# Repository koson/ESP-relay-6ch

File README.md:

# ESP-relay-6ch

ESP8266/ESP32 based board with 6x 24 VDC inputs and 6x 10A relay outputs.

This board is designed to be driven by an Olimex ESP32-POE, ESP32-POE-ISO or Wemos D1 Mini modules running Tasmota. In case the Wemos D1 Mini is used, the number of inputs and outputs will be limited to 4 each.

The design considers that the board will be mounted on a PCB DIN rail holder. The dimensions consider the holders offered by the Brazilian manufacturer Metaltex, check [here](https://www.metaltex.com.br/produtos/componentes/suportes/sp7-suporte-para-montagem-de-placa-de-circuito-impresso-em-trilho-din) for details.

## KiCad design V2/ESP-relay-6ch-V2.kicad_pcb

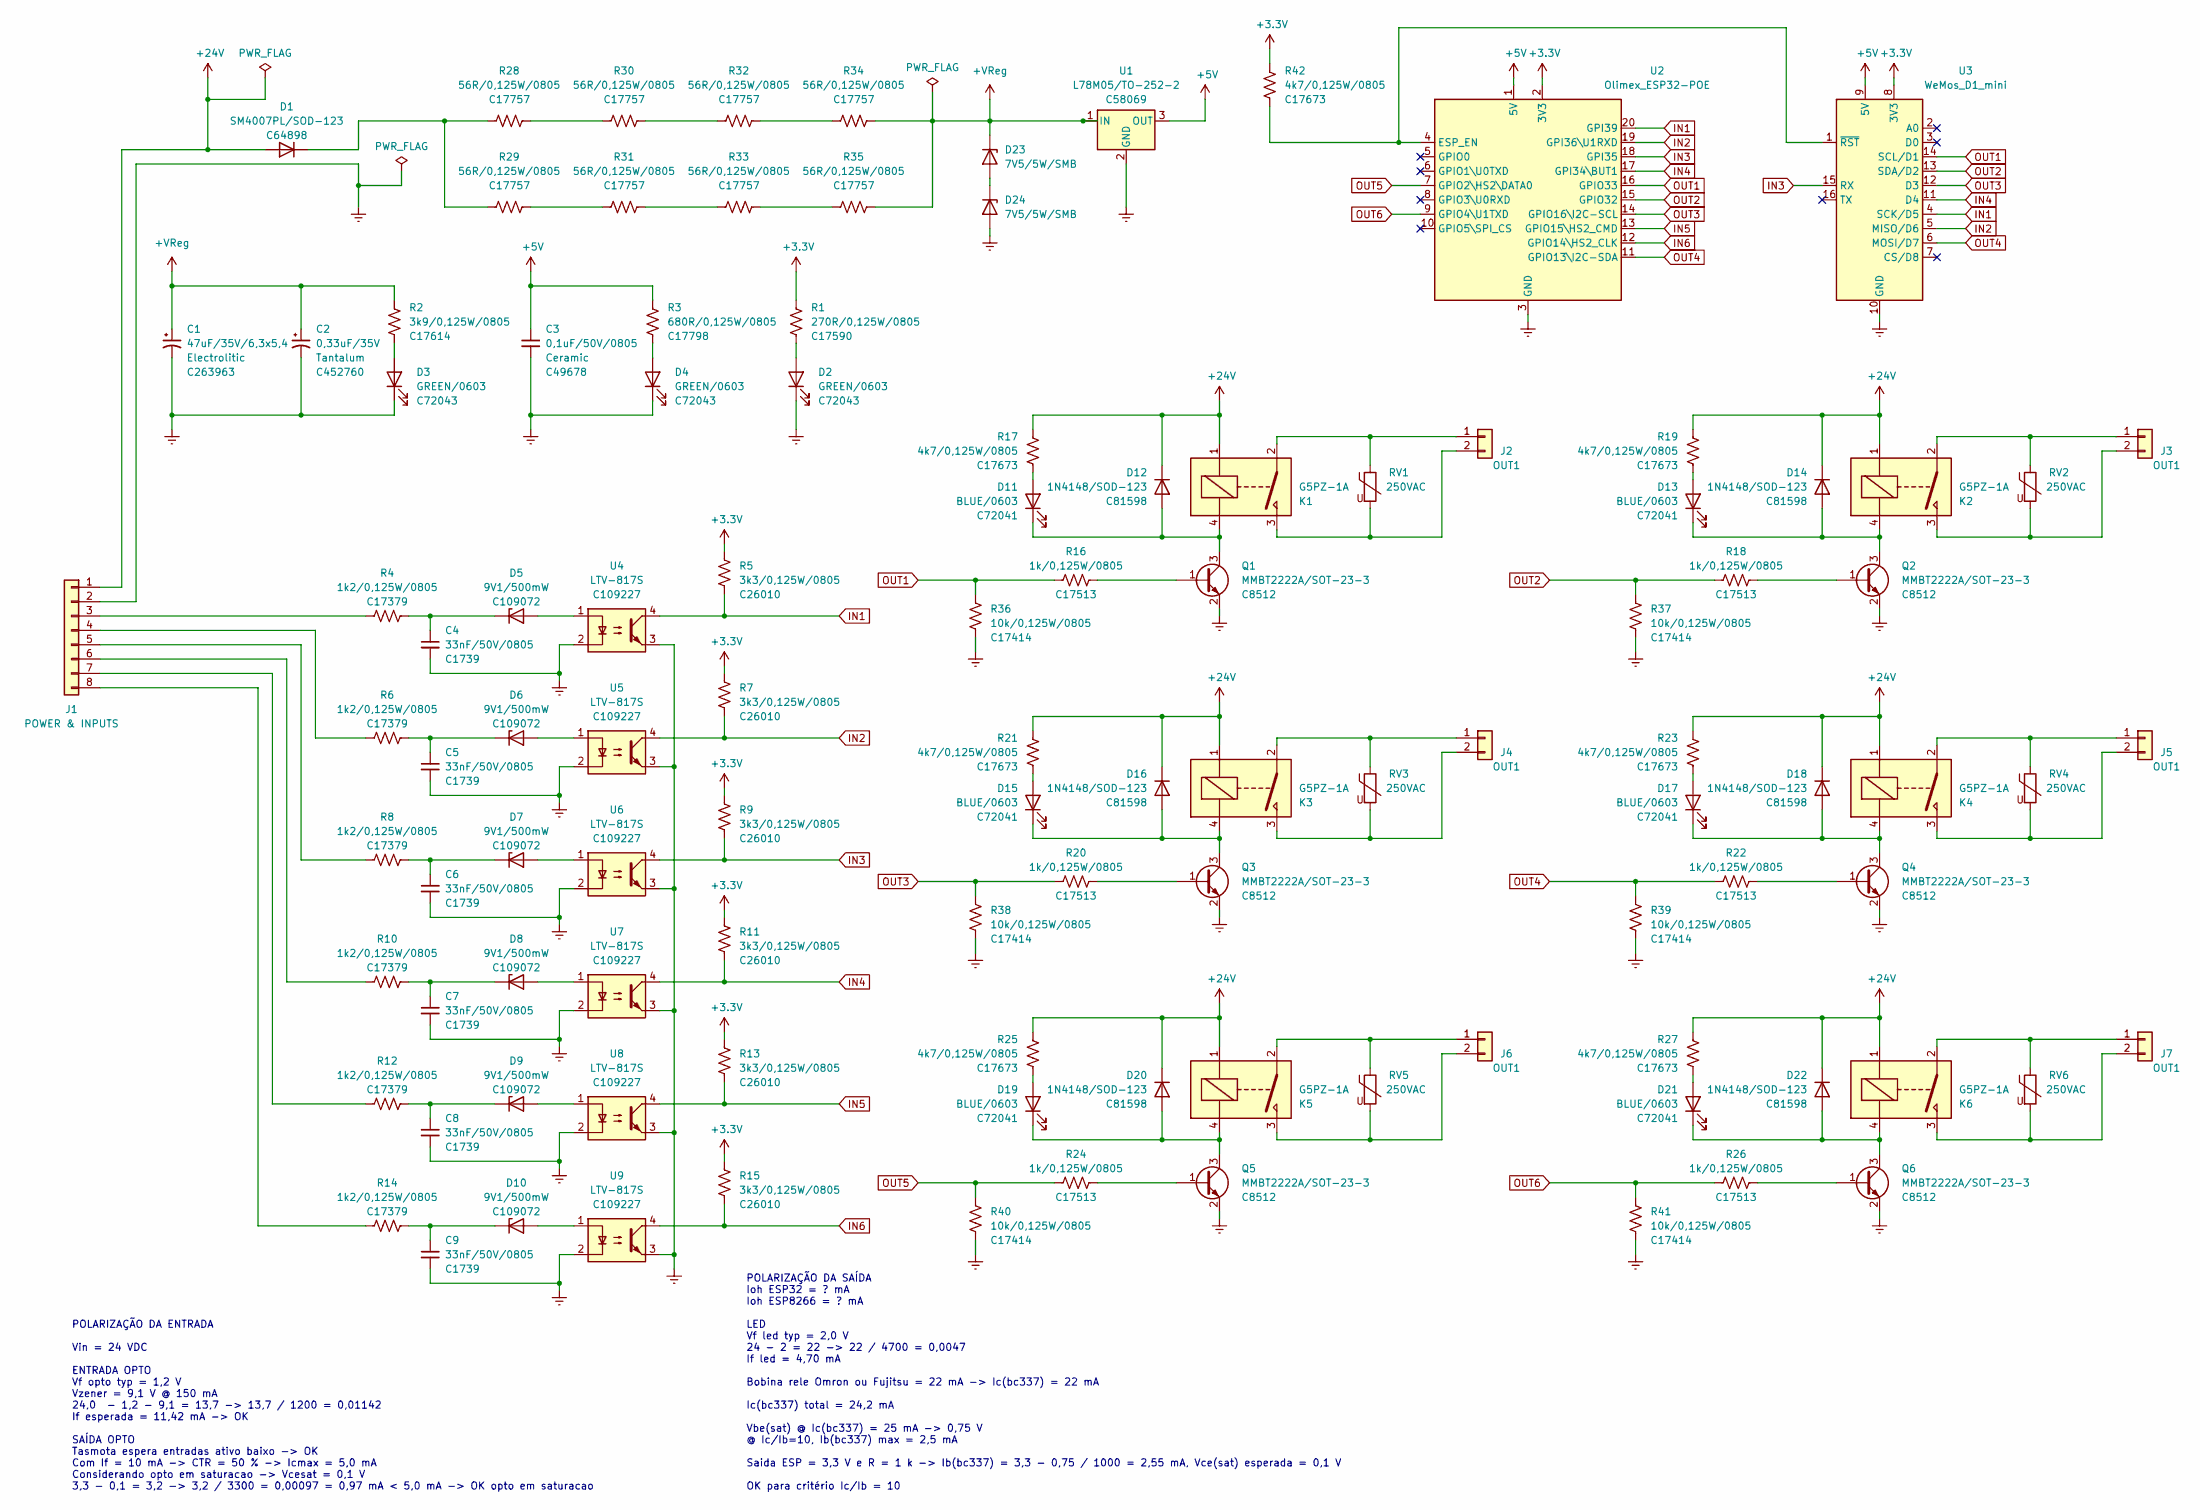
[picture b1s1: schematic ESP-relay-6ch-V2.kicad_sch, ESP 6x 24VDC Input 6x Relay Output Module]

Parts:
C1: 47uF/35V/6,3x5,4; CP_Elec_6.3x5.4; Mfr PN CK1V470MCRE54; JLCPCB BOM 1
C2: 0,33uF/35V; CP_EIA-3216-18_Kemet-A_Pad1.58x1.35mm_HandSolder; Mfr PN T491A334M035AT; JLCPCB BOM 1
C3: 0,1uF/50V/0805; C_0805_2012Metric; Mfr PN CC0805KRX7R9BB104; LCSC Part C49678
C4, C5, C6, C7, C8, C9: 33nF/50V/0805; C_0805_2012Metric; Mfr PN 0805B333K500NT; LCSC Part C1739
D1: SM4007PL/SOD-123; D_SOD-123; Mfr PN SM4007PL; LCSC Part C64898
D2, D3, D4: GREEN/0603; LED_0603_1608Metric; Mfr PN 19-217/GHC-YR1S2/3T; LCSC Part C72043
D5, D6, D7, D8, D9, D10: 9V1/500mW; D_MiniMELF; Mfr PN ZMM5239B; JLCPCB BOM 1
D11, D13, D15, D17, D19, D21: BLUE/0603; LED_0603_1608Metric; Mfr PN 19-217/BHC-ZL1M2RY/3T; LCSC Part C72041
D12, D14, D16, D18, D20, D22: 1N4148/SOD-123; D_SOD-123; Mfr PN 1N4148W; LCSC Part C81598
D23, D24: 7V5/5W/SMB; D_SMB; Mfr PN CZRB5343B-HF; JLCPCB BOM 0
J1: POWER & INPUTS; TerminalBlock_Phoenix_MKDS-3-8-5.08_1x08_P5.08mm_Horizontal; Mfr PN 3x BR902V; JLCPCB BOM 0
J2, J3, J4, J5, J6, J7: OUT1; TerminalBlock_Phoenix_MKDS-3-2-5.08_1x02_P5.08mm_Horizontal; Mfr PN BR902V; JLCPCB BOM 0
K1, K2, K3, K4, K5, K6: G5PZ-1A; Relay_SPST_Omron-G5PZ-1A; Mfr PN G5PZ-1A; JLCPCB BOM 0
Q1, Q2, Q3, Q4, Q5, Q6: MMBT2222A/SOT-23-3; SOT-23; Mfr PN MMBT2222A; JLCPCB BOM 1
R1: 270R/0,125W/0805; R_0805_2012Metric; Mfr PN 0805W8F2700T5E; LCSC Part C17590
R2: 3k9/0,125W/0805; R_0805_2012Metric; Mfr PN 0805W8F3901T5E; LCSC Part C17614
R3: 680R/0,125W/0805; R_0805_2012Metric; Mfr PN 0805W8F6800T5E; LCSC Part C17798
R4, R6, R8, R10, R12, R14: 1k2/0,125W/0805; R_0805_2012Metric; Mfr PN 0805W8F1201T5E; LCSC Part C17379
R5, R7, R9, R11, R13, R15: 3k3/0,125W/0805; R_0805_2012Metric; Mfr PN 0805W8F3301T5E; LCSC Part C26010
R16, R18, R20, R22, R24, R26: 1k/0,125W/0805; R_0805_2012Metric; Mfr PN 0805W8F1001T5E; LCSC Part C17513
R17, R19, R21, R23, R25, R27: 4k7/0,125W/0805; R_0805_2012Metric; Mfr PN 0805W8F4701T5E; LCSC Part C17673
R28, R29, R30, R31, R32, R33, R34, R35: 56R/0,125W/0805; R_0805_2012Metric; Mfr PN 0805W8F560JT5E; JLCPCB BOM 1
R36, R37, R38, R39, R40, R41: 10k/0,125W/0805; R_0805_2012Metric; Mfr PN 0805W8F3301T5E; LCSC Part C17414
R42: 4k7/0,125W/0805; R_0805_2012Metric; Mfr PN 0805W8F2700T5E; LCSC Part C17673
RV1, RV2, RV3, RV4, RV5, RV6: 250VAC; RV_Disc_D12mm_W3.9mm_P7.5mm; Mfr PN 391KD10; JLCPCB BOM 0
U1: L78M05/TO-252-2; TO-252-2; Mfr PN L78M05ABDT-TR; LCSC Part C58069
U2: Olimex_ESP32-POE; Olimex_ESP32-POE_Pads; Mfr PN ESP32-POE; JLCPCB BOM 0
U3: WeMos_D1_mini; WEMOS_D1_mini_light_pads; Mfr PN D1 Mini Node MCU; JLCPCB BOM 0
U4, U5, U6, U7, U8, U9: LTV-817S; SMDIP-4_W9.53mm; Mfr PN LTV-817S-TA1-C; JLCPCB BOM 1

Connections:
+3V3: R1.1, R5.1, R7.1, R9.1, R11.1, R13.1, R15.1, R42.1, U2.2 (3V3), U3.8 (3V3)
+5V: C3.1, R3.1, U1.3 (OUT), U2.1 (5V), U3.9 (5V)
+24V: D1.2 (A), D12.1 (K), D14.1 (K), D16.1 (K), D18.1 (K), D20.1 (K), D22.1 (K), J1.1, K1.1, K2.1, K3.1, K4.1, K5.1, K6.1, R17.1, R19.1, R21.1, R23.1, R25.1, R27.1
+VReg: C1.1, C2.1, D23.1 (K), R2.1, R34.2, R35.2, U1.1 (IN)
GNDREF: C1.2, C2.2, C3.2, C4.2, C5.2, C6.2, C7.2, C8.2, C9.2, D2.1 (K), D3.1 (K), D4.1 (K), D24.2 (A), J1.2, Q1.2 (E), Q2.2 (E), Q3.2 (E), Q4.2 (E), Q5.2 (E), Q6.2 (E), R36.2, R37.2, R38.2, R39.2, R40.2, R41.2, U1.2 (GND), U2.3 (GND), U3.10 (GND), U4.2, U4.3, U5.2, U5.3, U6.2, U6.3, U7.2, U7.3, U8.2, U8.3, U9.2, U9.3
IN1: R5.2, U2.20 (GPI39), U3.4 (SCK/D5), U4.4
IN2: R7.2, U2.19 (GPI36\U1RXD), U3.5 (MISO/D6), U5.4
IN3: R9.2, U2.18 (GPI35), U3.15 (RX), U6.4
IN4: R11.2, U2.17 (GPI34\BUT1), U3.11 (D4), U7.4
IN5: R13.2, U2.13 (GPIO15\HS2_CMD), U8.4
IN6: R15.2, U2.12 (GPIO14\HS2_CLK), U9.4
unnamed: C4.1, D5.1 (K), R4.1
unnamed: C5.1, D6.1 (K), R6.1
unnamed: C6.1, D7.1 (K), R8.1
unnamed: C7.1, D8.1 (K), R10.1
unnamed: C8.1, D9.1 (K), R12.1
unnamed: C9.1, D10.1 (K), R14.1
unnamed: D1.1 (K), R28.1, R29.1
unnamed: D2.2 (A), R1.2
unnamed: D3.2 (A), R2.2
unnamed: D4.2 (A), R3.2
unnamed: D5.2 (A), U4.1
unnamed: D6.2 (A), U5.1
unnamed: D7.2 (A), U6.1
unnamed: D8.2 (A), U7.1
unnamed: D9.2 (A), U8.1
unnamed: D10.2 (A), U9.1
unnamed: D11.1 (K), D12.2 (A), K1.4, Q1.3 (C)
unnamed: D11.2 (A), R17.2
unnamed: D13.1 (K), D14.2 (A), K2.4, Q2.3 (C)
unnamed: D13.2 (A), R19.2
unnamed: D15.1 (K), D16.2 (A), K3.4, Q3.3 (C)
unnamed: D15.2 (A), R21.2
unnamed: D17.1 (K), D18.2 (A), K4.4, Q4.3 (C)
unnamed: D17.2 (A), R23.2
unnamed: D19.1 (K), D20.2 (A), K5.4, Q5.3 (C)
unnamed: D19.2 (A), R25.2
unnamed: D21.1 (K), D22.2 (A), K6.4, Q6.3 (C)
unnamed: D21.2 (A), R27.2
unnamed: D23.2 (A), D24.1 (K)
unnamed: J1.3, R4.2
unnamed: J1.4, R6.2
unnamed: J1.5, R8.2
unnamed: J1.6, R10.2
unnamed: J1.7, R12.2
unnamed: J1.8, R14.2
unnamed: J2.1, K1.2, RV1.1
unnamed: J2.2, K1.3, RV1.2
unnamed: J3.1, K2.2, RV2.1
unnamed: J3.2, K2.3, RV2.2
unnamed: J4.1, K3.2, RV3.1
unnamed: J4.2, K3.3, RV3.2
unnamed: J5.1, K4.2, RV4.1
unnamed: J5.2, K4.3, RV4.2
unnamed: J6.1, K5.2, RV5.1
unnamed: J6.2, K5.3, RV5.2
unnamed: J7.1, K6.2, RV6.1
unnamed: J7.2, K6.3, RV6.2
unnamed: Q1.1 (B), R16.1
unnamed: Q2.1 (B), R18.1
unnamed: Q3.1 (B), R20.1
unnamed: Q4.1 (B), R22.1
unnamed: Q5.1 (B), R24.1
unnamed: Q6.1 (B), R26.1
unnamed: R28.2, R30.1
unnamed: R29.2, R31.1
unnamed: R30.2, R32.1
unnamed: R31.2, R33.1
unnamed: R32.2, R34.1
unnamed: R33.2, R35.1
unnamed: R42.2, U2.4 (ESP_EN), U3.1 (~RST)
OUT1: R16.2, R36.1, U2.16 (GPIO33), U3.14 (SCL/D1)
OUT2: R18.2, R37.1, U2.15 (GPIO32), U3.13 (SDA/D2)
OUT3: R20.2, R38.1, U2.14 (GPIO16\I2C-SCL), U3.12 (D3)
OUT4: R22.2, R39.1, U2.11 (GPIO13\I2C-SDA), U3.6 (MOSI/D7)
OUT5: R24.2, R40.1, U2.7 (GPIO2\HS2\DATA0)
OUT6: R26.2, R41.1, U2.9 (GPIO4\U1TXD)

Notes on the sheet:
POLARIZAÇÃO DA ENTRADA Vin = 24 VDC ENTRADA OPTO Vf opto typ = 1,2 V Vzener = 9,1 V @ 150 mA 24,0 - 1,2 - 9,1 = 13,7 -> 13,7 / 1200 = 0,01142 If esperada = 11,42 mA -> OK SAÍDA OPTO Tasmota espera entradas ativo baixo -> OK Com If = 10 mA -> CTR = 50 % -> Icmax = 5,0 mA Considerando opto em saturac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
POLARIZAÇÃO DA SAÍDA Ioh ESP32 = ? mA Ioh ESP8266 = ? mA LED Vf led typ = 2,0 V 24 - 2 = 22 -> 22 / 4700 = 0,0047 If led = 4,70 mA Bobina rele Omron ou Fujitsu = 22 mA -> Ic(bc337) = 22 mA Ic(bc337) total = 24,2 mA Vbe(sat) @ Ic(bc337) = 25 mA -> 0,75 V @ Ic/Ib=10, Ib(bc337) max = 2,5 mA Saida ESP 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

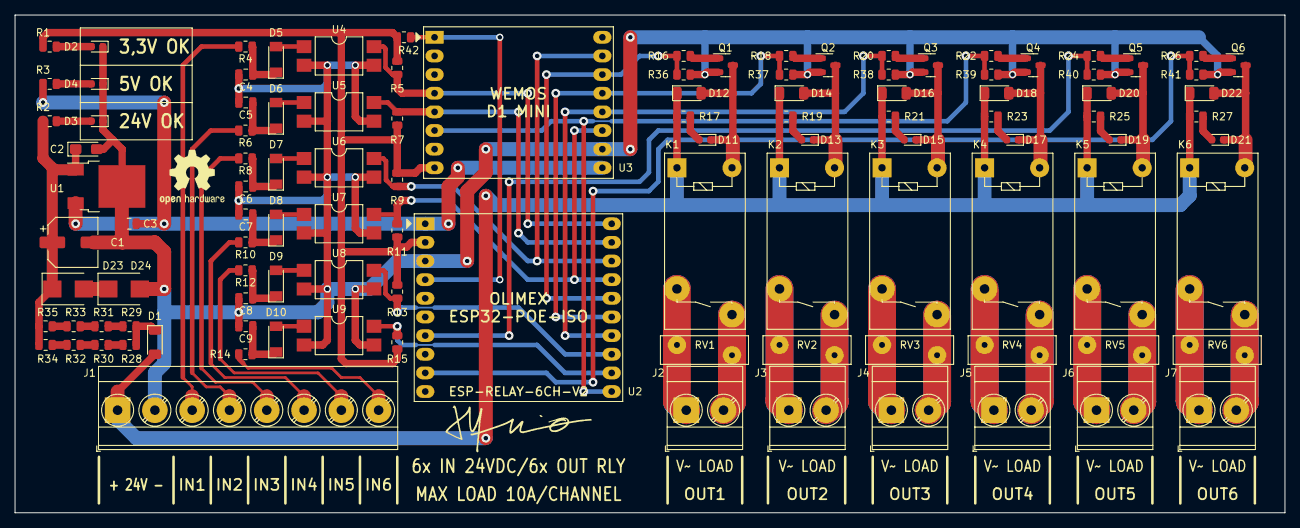
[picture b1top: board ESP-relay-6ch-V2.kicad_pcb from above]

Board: 2 copper layers, 173.0 x 67.8 mm, 109 parts (0 on the bottom side), 77 nets.

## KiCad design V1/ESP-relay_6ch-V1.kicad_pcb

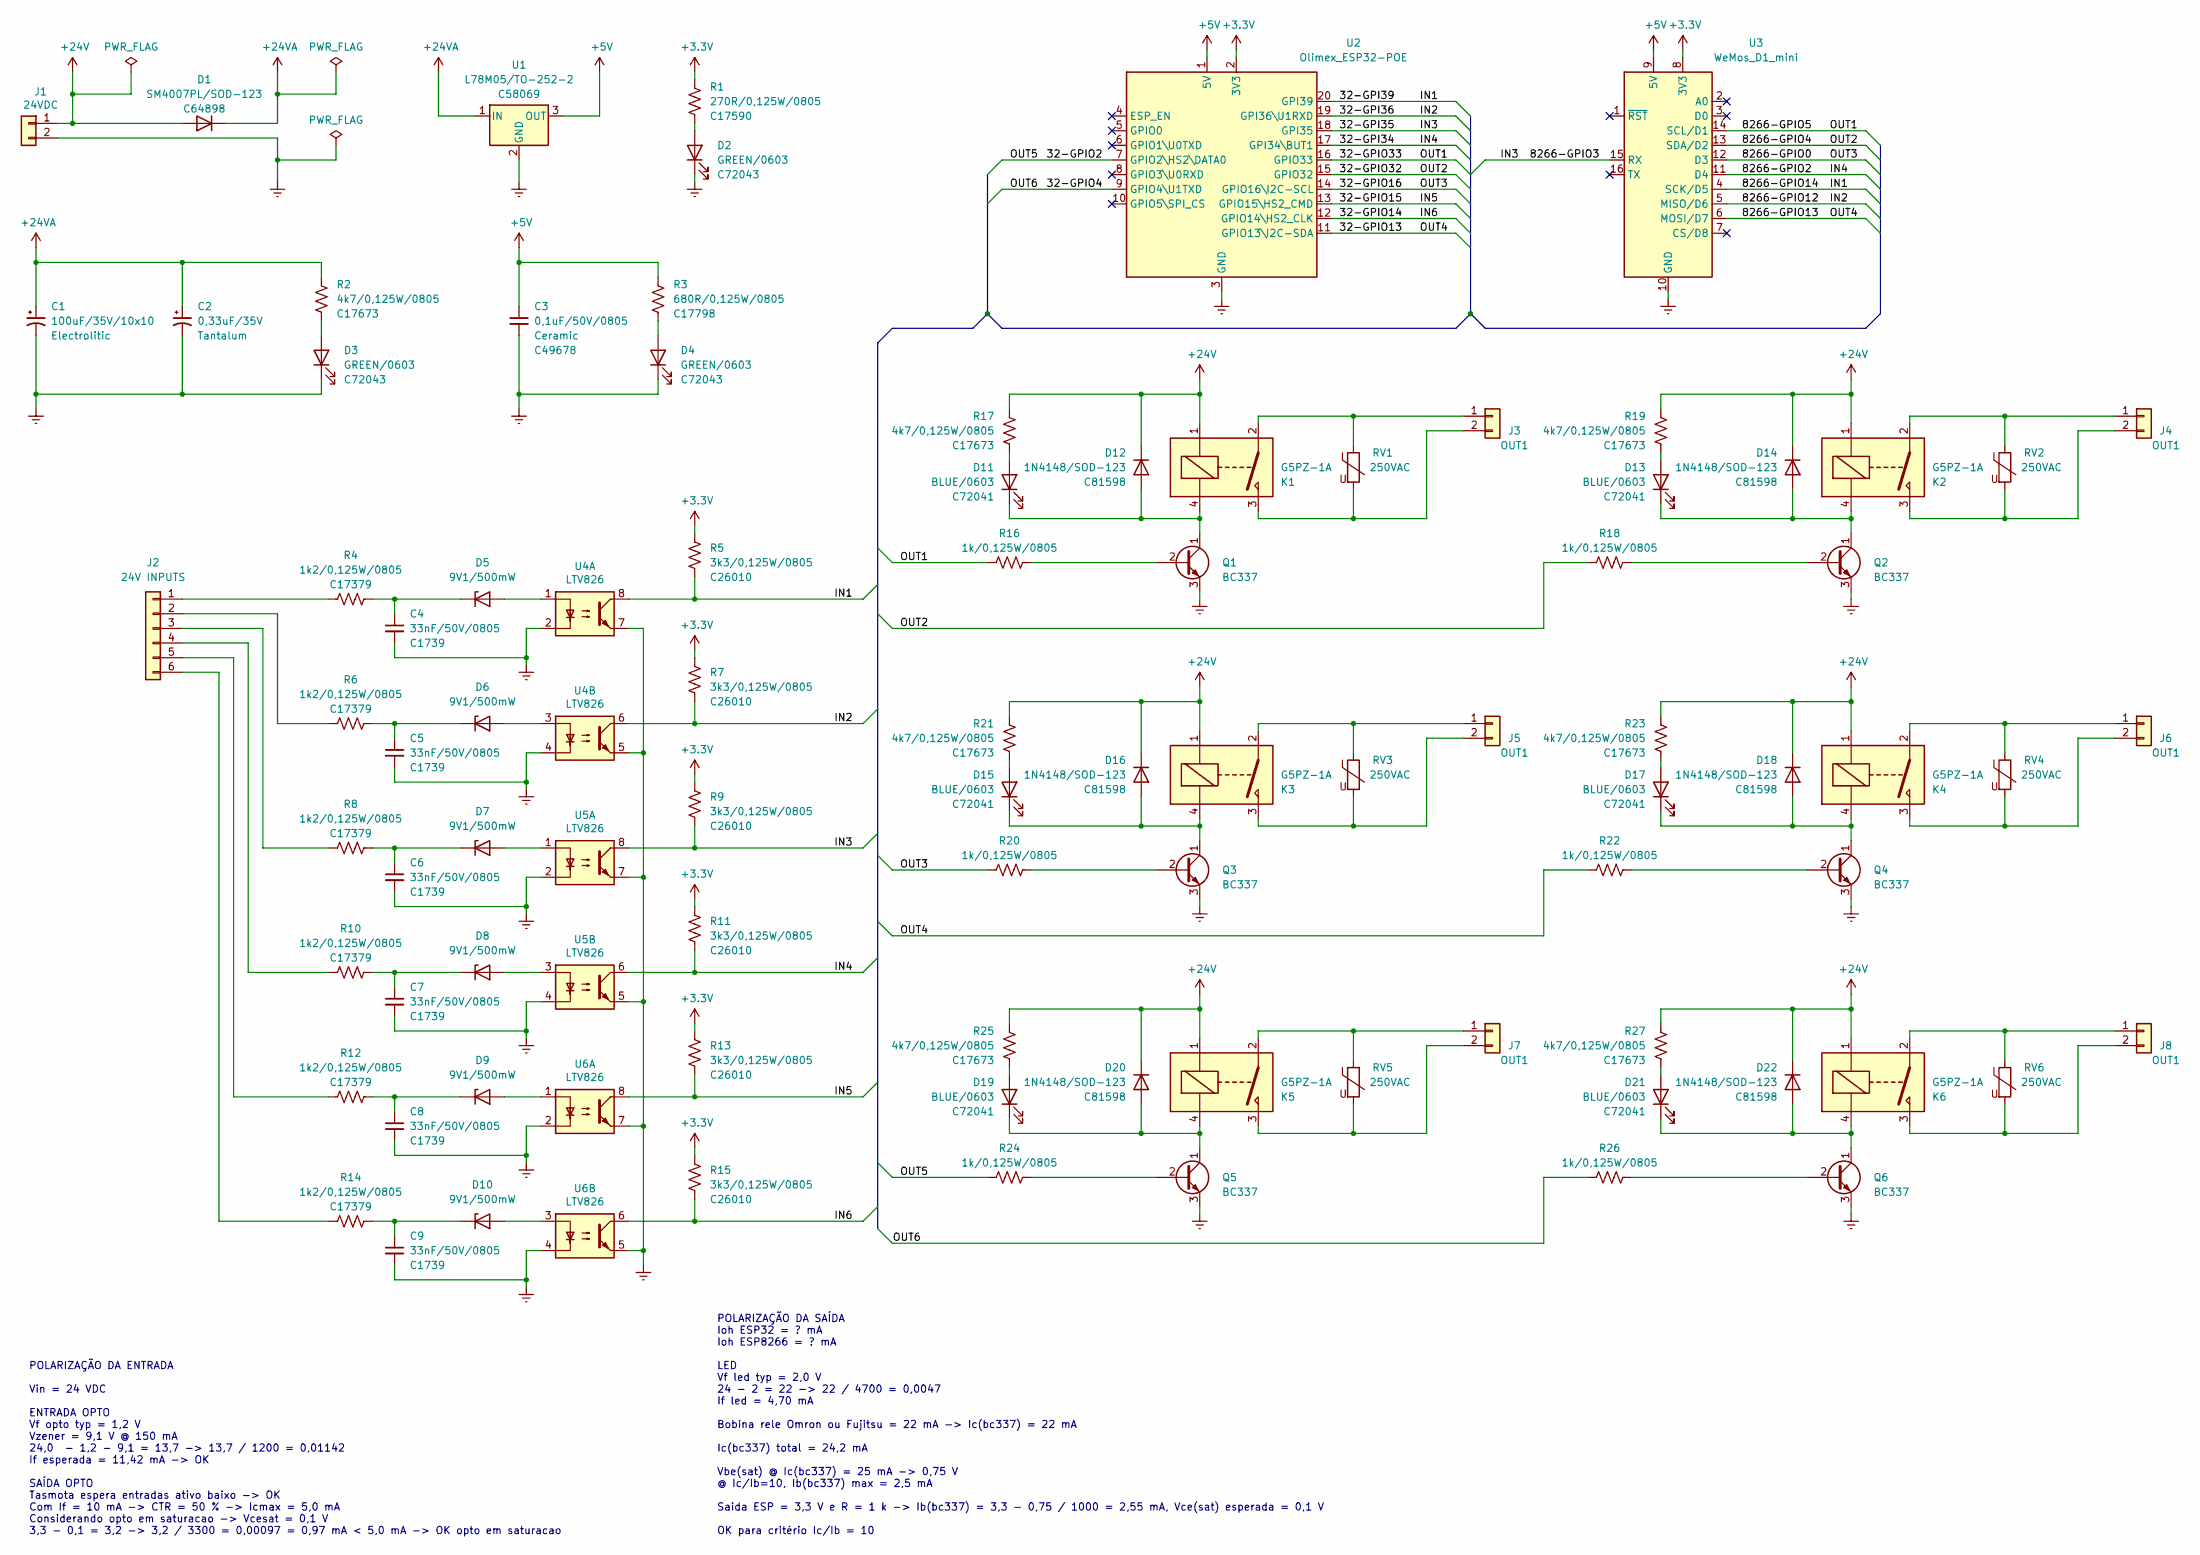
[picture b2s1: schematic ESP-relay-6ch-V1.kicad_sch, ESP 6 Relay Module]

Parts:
C1: 100uF/35V/10x10; CP_Elec_10x10; Mfr PN MAL214097001E3; JLCPCB BOM 0
C2: 0,33uF/35V; CP_EIA-3216-18_Kemet-A_Pad1.58x1.35mm_HandSolder; Mfr PN TAJA334K035RNJ; JLCPCB BOM 0
C3: 0,1uF/50V/0805; C_0805_2012Metric; Mfr PN CC0805KRX7R9BB104; LCSC Part C49678
C4, C5, C6, C7, C8, C9: 33nF/50V/0805; C_0805_2012Metric; Mfr PN 0805B333K500NT; LCSC Part C1739
D1: SM4007PL/SOD-123; D_SOD-123; Mfr PN SM4007PL; LCSC Part C64898
D2, D3, D4: GREEN/0603; LED_0603_1608Metric; Mfr PN 19-217/GHC-YR1S2/3T; LCSC Part C72043
D5, D6, D7, D8, D9, D10: 9V1/500mW; D_SOD-323; Mfr PN MM3Z9V1T1G; JLCPCB BOM 0
D11, D13, D15, D17, D19, D21: BLUE/0603; LED_0603_1608Metric; Mfr PN 19-217/BHC-ZL1M2RY/3T; LCSC Part C72041
D12, D14, D16, D18, D20, D22: 1N4148/SOD-123; D_SOD-123; Mfr PN 1N4148W; LCSC Part C81598
J1: 24VDC; TerminalBlock_Phoenix_MKDS-3-2-5.08_1x02_P5.08mm_Horizontal; Mfr PN BR902V; JLCPCB BOM 0
J2: 24V INPUTS; TerminalBlock_Phoenix_MKDS-3-6-5.08_1x06_P5.08mm_Horizontal; Mfr PN 3x BR902V; JLCPCB BOM 0
J3, J4, J5, J6, J7, J8: OUT1; TerminalBlock_Phoenix_MKDS-3-2-5.08_1x02_P5.08mm_Horizontal; Mfr PN BR902V; JLCPCB BOM 0
K1, K2, K3, K4, K5, K6: G5PZ-1A; Relay_SPST_Omron-G5PZ-1A; Mfr PN G5PZ-1A; JLCPCB BOM 0
Q1, Q2, Q3, Q4, Q5, Q6: BC337; TO-92_Inline_Wide; Mfr PN BC337-25; JLCPCB BOM 0
R1: 270R/0,125W/0805; R_0805_2012Metric; Mfr PN 0805W8F2700T5E; LCSC Part C17590
R2, R17, R19, R21, R23, R25, R27: 4k7/0,125W/0805; R_0805_2012Metric; Mfr PN 0805W8F4701T5E; LCSC Part C17673
R3: 680R/0,125W/0805; R_0805_2012Metric; Mfr PN 0805W8F6800T5E; LCSC Part C17798
R4, R6, R8, R10, R12, R14: 1k2/0,125W/0805; R_0805_2012Metric; Mfr PN 0805W8F1201T5E; LCSC Part C17379
R5, R7, R9, R11, R13, R15: 3k3/0,125W/0805; R_0805_2012Metric; Mfr PN 0805W8F3301T5E; LCSC Part C26010
R16, R18, R20, R22, R24, R26: 1k/0,125W/0805; R_0805_2012Metric; Mfr PN 0805W8F1001T5E; LCSC Part C17513
RV1, RV2, RV3, RV4, RV5, RV6: 250VAC; RV_Disc_D12mm_W3.9mm_P7.5mm; Mfr PN 391KD10; JLCPCB BOM 0
U1: L78M05/TO-252-2; TO-252-2; Mfr PN L78M05ABDT-TR; LCSC Part C58069
U2: Olimex_ESP32-POE; Olimex_ESP32-POE_Pads; Mfr PN ESP32-POE; JLCPCB BOM 0
U3: WeMos_D1_mini; WEMOS_D1_mini_light_pads; Mfr PN D1 Mini Node MCU; JLCPCB BOM 0
U4, U5, U6: LTV826; DIP-8_W7.62mm; Mfr PN LTV-826; JLCPCB BOM 0

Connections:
+3V3: R1.1, R5.1, R7.1, R9.1, R11.1, R13.1, R15.1, U2.2 (3V3), U3.8 (3V3)
+5V: C3.1, R3.1, U1.3 (OUT), U2.1 (5V), U3.9 (5V)
+24V: D1.2 (A), D12.1 (K), D14.1 (K), D16.1 (K), D18.1 (K), D20.1 (K), D22.1 (K), J1.1, K1.1, K2.1, K3.1, K4.1, K5.1, K6.1, R17.1, R19.1, R21.1, R23.1, R25.1, R27.1
+24VA: C1.1, C2.1, D1.1 (K), R2.1, U1.1 (IN)
/32-GPI34: R11.2, U2.17 (GPI34\BUT1), U3.11 (D4), U5.6
/32-GPI35: R9.2, U2.18 (GPI35), U3.15 (RX), U5.8
/32-GPI36: R7.2, U2.19 (GPI36\U1RXD), U3.5 (MISO/D6), U4.6
/32-GPI39: R5.2, U2.20 (GPI39), U3.4 (SCK/D5), U4.8
/32-GPIO2: R24.2, U2.7 (GPIO2\HS2\DATA0)
/32-GPIO4: R26.2, U2.9 (GPIO4\U1TXD)
/32-GPIO13: R22.2, U2.11 (GPIO13\I2C-SDA), U3.6 (MOSI/D7)
/32-GPIO14: R15.2, U2.12 (GPIO14\HS2_CLK), U6.6
/32-GPIO15: R13.2, U2.13 (GPIO15\HS2_CMD), U6.8
/32-GPIO16: R20.2, U2.14 (GPIO16\I2C-SCL), U3.12 (D3)
/32-GPIO32: R18.2, U2.15 (GPIO32), U3.13 (SDA/D2)
/32-GPIO33: R16.2, U2.16 (GPIO33), U3.14 (SCL/D1)
GNDREF: C1.2, C2.2, C3.2, C4.2, C5.2, C6.2, C7.2, C8.2, C9.2, D2.1 (K), D3.1 (K), D4.1 (K), J1.2, Q1.3 (E), Q2.3 (E), Q3.3 (E), Q4.3 (E), Q5.3 (E), Q6.3 (E), U1.2 (GND), U2.3 (GND), U3.10 (GND), U4.2, U4.4, U4.5, U4.7, U5.2, U5.4, U5.5, U5.7, U6.2, U6.4, U6.5, U6.7
unnamed: C4.1, D5.1 (K), R4.1
unnamed: C5.1, D6.1 (K), R6.1
unnamed: C6.1, D7.1 (K), R8.1
unnamed: C7.1, D8.1 (K), R10.1
unnamed: C8.1, D9.1 (K), R12.1
unnamed: C9.1, D10.1 (K), R14.1
unnamed: D2.2 (A), R1.2
unnamed: D3.2 (A), R2.2
unnamed: D4.2 (A), R3.2
unnamed: D5.2 (A), U4.1
unnamed: D6.2 (A), U4.3
unnamed: D7.2 (A), U5.1
unnamed: D8.2 (A), U5.3
unnamed: D9.2 (A), U6.1
unnamed: D10.2 (A), U6.3
unnamed: D11.1 (K), D12.2 (A), K1.4, Q1.1 (C)
unnamed: D11.2 (A), R17.2
unnamed: D13.1 (K), D14.2 (A), K2.4, Q2.1 (C)
unnamed: D13.2 (A), R19.2
unnamed: D15.1 (K), D16.2 (A), K3.4, Q3.1 (C)
unnamed: D15.2 (A), R21.2
unnamed: D17.1 (K), D18.2 (A), K4.4, Q4.1 (C)
unnamed: D17.2 (A), R23.2
unnamed: D19.1 (K), D20.2 (A), K5.4, Q5.1 (C)
unnamed: D19.2 (A), R25.2
unnamed: D21.1 (K), D22.2 (A), K6.4, Q6.1 (C)
unnamed: D21.2 (A), R27.2
unnamed: J2.1, R4.2
unnamed: J2.2, R6.2
unnamed: J2.3, R8.2
unnamed: J2.4, R10.2
unnamed: J2.5, R12.2
unnamed: J2.6, R14.2
unnamed: J3.1, K1.2, RV1.1
unnamed: J3.2, K1.3, RV1.2
unnamed: J4.1, K2.2, RV2.1
unnamed: J4.2, K2.3, RV2.2
unnamed: J5.1, K3.2, RV3.1
unnamed: J5.2, K3.3, RV3.2
unnamed: J6.1, K4.2, RV4.1
unnamed: J6.2, K4.3, RV4.2
unnamed: J7.1, K5.2, RV5.1
unnamed: J7.2, K5.3, RV5.2
unnamed: J8.1, K6.2, RV6.1
unnamed: J8.2, K6.3, RV6.2
unnamed: Q1.2 (B), R16.1
unnamed: Q2.2 (B), R18.1
unnamed: Q3.2 (B), R20.1
unnamed: Q4.2 (B), R22.1
unnamed: Q5.2 (B), R24.1
unnamed: Q6.2 (B), R26.1

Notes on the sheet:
POLARIZAÇÃO DA ENTRADA Vin = 24 VDC ENTRADA OPTO Vf opto typ = 1,2 V Vzener = 9,1 V @ 150 mA 24,0 - 1,2 - 9,1 = 13,7 -> 13,7 / 1200 = 0,01142 If esperada = 11,42 mA -> OK SAÍDA OPTO Tasmota espera entradas ativo baixo -> OK Com If = 10 mA -> CTR = 50 % -> Icmax = 5,0 mA Considerando opto em saturac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
POLARIZAÇÃO DA SAÍDA Ioh ESP32 = ? mA Ioh ESP8266 = ? mA LED Vf led typ = 2,0 V 24 - 2 = 22 -> 22 / 4700 = 0,0047 If led = 4,70 mA Bobina rele Omron ou Fujitsu = 22 mA -> Ic(bc337) = 22 mA Ic(bc337) total = 24,2 mA Vbe(sat) @ Ic(bc337) = 25 mA -> 0,75 V @ Ic/Ib=10, Ib(bc337) max = 2,5 mA Saida ESP 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

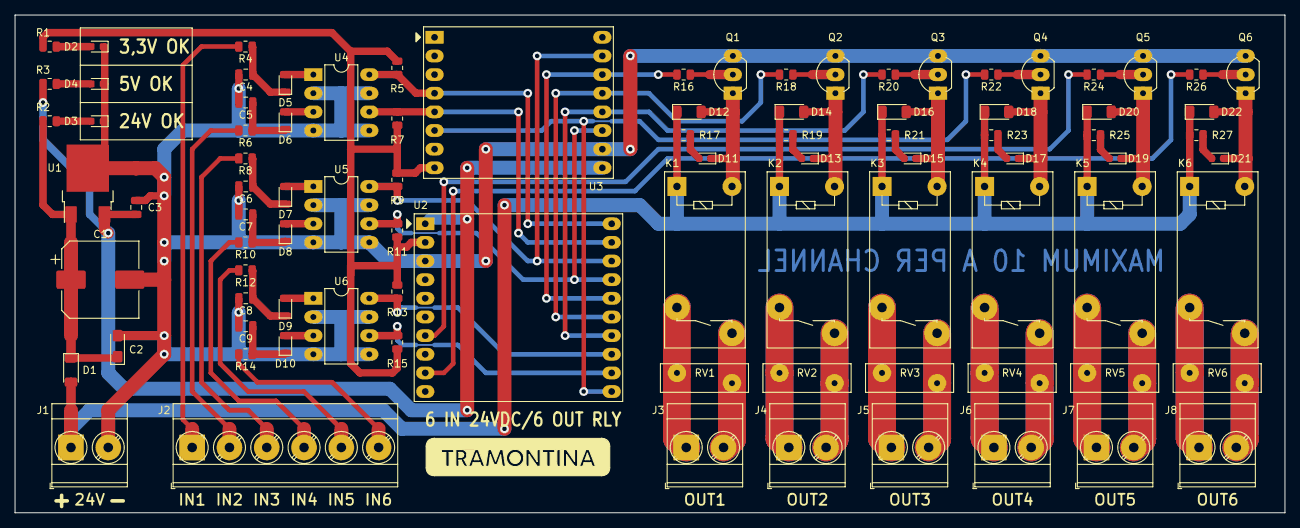
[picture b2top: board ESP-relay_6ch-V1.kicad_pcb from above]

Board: 2 copper layers, 173.0 x 67.8 mm, 90 parts (0 on the bottom side), 68 nets.

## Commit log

2022-02-02 Initial upload
2022-02-28 Cleanup after migration to Kicad 6
2022-03-06 V2 development
2022-03-06 cleaning up
2022-03-07 footprint updates
2022-03-08 tweaks
2022-03-29 work in progress
2022-04-01 add pull down resistors
2022-04-01 PCB tweaks
2022-04-01 Upload backups
2022-04-03 rename files to new schema
2022-04-13 update schematics title block
